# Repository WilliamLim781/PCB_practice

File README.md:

# PCB_practice
just a bunch of PCB practice. That's it

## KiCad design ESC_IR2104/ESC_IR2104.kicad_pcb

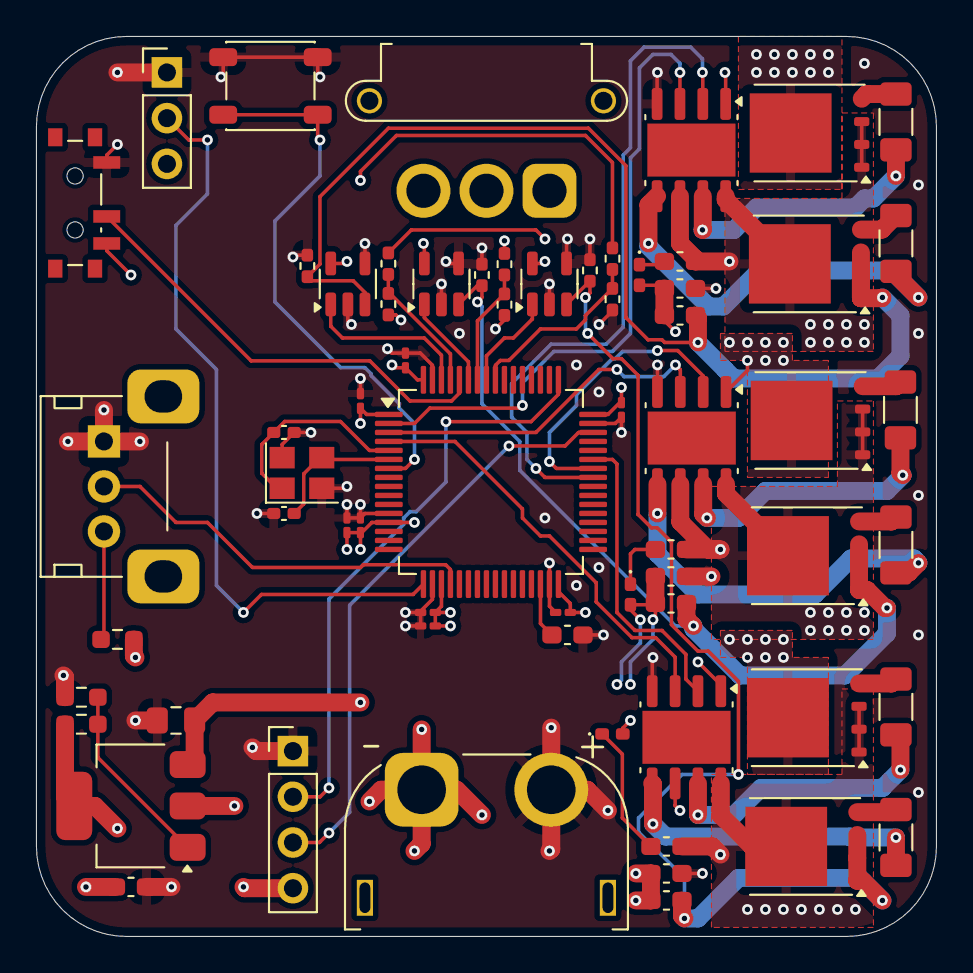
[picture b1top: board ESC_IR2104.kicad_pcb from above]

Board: 6 copper layers, 50.0 x 50.0 mm, 65 parts (0 on the bottom side), 47 nets.

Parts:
C1: 4.7u; C_0201_0603Metric_Pad0.64x0.40mm_HandSolder
C2, C3, C4, C5, C6, C7: 100n; C_0201_0603Metric_Pad0.64x0.40mm_HandSolder
C8: 1u; C_0201_0603Metric_Pad0.64x0.40mm_HandSolder
C9, C10: 8p; C_0402_1005Metric_Pad0.74x0.62mm_HandSolder
C11, C16, C19, C22: 4u7; C_0603_1608Metric_Pad1.08x0.95mm_HandSolder
C12: 10u; C_0805_2012Metric_Pad1.18x1.45mm_HandSolder
C13: 22u; C_0603_1608Metric_Pad1.08x0.95mm_HandSolder
C14, C17, C20: 100n 50V; C_0603_1608Metric_Pad1.08x0.95mm_HandSolder
C15: .27u 50v; C_0603_1608Metric_Pad1.08x0.95mm_HandSolder
C18, C21: .027u 50v; C_0603_1608Metric_Pad1.08x0.95mm_HandSolder
D1, D2, D3: D; D_0402_1005Metric_Pad0.77x0.64mm_HandSolder
J1: swd; PinHeader_1x04_P2.54mm_Vertical
J2: input; PinHeader_1x03_P2.54mm_Vertical
J3: Conn_01x03; AMASS_MR30PW-FB_1x03_P3.50mm_Horizontal
J4: Conn_01x02_Socket; AMASS_XT60PW-F_1x02_P7.20mm_Horizontal
Q1, Q2, Q3, Q4, Q5, Q6: BSC028N06LS3; TDSON-8-1
R1: Current limiter; R_0603_1608Metric_Pad0.98x0.95mm_HandSolder
R2: 10k; R_0603_1608Metric_Pad0.98x0.95mm_HandSolder
R3: 11k; R_0603_1608Metric_Pad0.98x0.95mm_HandSolder
R4, R5, R9, R10, R14, R15: 100; R_1206_3216Metric_Pad1.30x1.75mm_HandSolder
R6, R11, R16: 100k; R_0402_1005Metric_Pad0.72x0.64mm_HandSolder
R7, R12, R17: 2m; R_0402_1005Metric_Pad0.72x0.64mm_HandSolder
R8, R13, R18: 22K; R_0402_1005Metric_Pad0.72x0.64mm_HandSolder
RV1: pot; Potentiometer_Alps_RK09K_Single_Horizontal
SW1: NRST; SW_SPST_PTS647_Sx38
SW2: Boot0; SW_SPDT_PCM12
U1: STM32F411RETx; LQFP-64_10x10mm_P0.5mm
U2: AMS1117; SOT-223-3_TabPin2
U3, U5, U7: IR2104; SOIC-8-1EP_3.9x4.9mm_P1.27mm_EP2.95x4.9mm_Mask2.71x3.4mm
U4, U6, U8: INA180A1; SOT-23-5
Y1: 16Mhz?; Crystal_SMD_3225-4Pin_3.2x2.5mm

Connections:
+3.3V: C1.1, C2.1, C3.1, C4.1, C5.1, C6.1, C7.1, C8.1, C13.1, J1.4, J2.3, R1.1, R2.1, SW2.3 (C), U1.1 (VBAT), U1.13 (VDDA), U1.19 (VDD), U1.32 (VDD), U1.48 (VDD), U1.64 (VDD), U2.2 (VO), U4.5 (V+), U6.5 (V+), U8.5 (V+)
/ADC1_IN4: RV1.2, U1.20 (PA4)
/MosFet TIM_1_PhaseA/LowsideA: C16.2, Q2.1 (S), Q2.2 (S), Q2.3 (S), R7.1, U4.3 (+)
/MosFet TIM_1_PhaseB/LowsideA: C19.2, Q4.1 (S), Q4.2 (S), Q4.3 (S), R12.1, U6.3 (+)
/MosFet TIM_1_PhaseC/LowsideA: C22.2, Q6.1 (S), Q6.2 (S), Q6.3 (S), R17.1, U8.3 (+)
GND: C1.2, C2.2, C3.2, C4.2, C5.2, C6.2, C7.2, C8.2, C9.2, C10.2, C11.2, C12.2, C13.2, C14.1, C17.1, C20.1, J1.1, J2.1, J4.2, R3.2, R7.2, R8.2, R12.2, R13.2, R17.2, R18.2, RV1.1, SW1.1 (A), SW2.1 (A), U1.12 (VSSA), U1.18 (VSS), U1.31 (VSS), U1.47 (VSS), U1.63 (VSS), U3.4 (COM), U4.2 (GND), U4.4 (-), U5.4 (COM), U6.2 (GND), U6.4 (-), U7.4 (COM), U8.2 (GND), U8.4 (-), Y1.2, Y1.4
HSE_IN: C9.1, U1.5 (PH0), Y1.1
HSE_OUT: C10.1, U1.6 (PH1), Y1.3
unnamed: C15.2, D1.1 (K)
unnamed: C18.2, D2.1 (K)
unnamed: C21.2, D3.1 (K)
unnamed: Q1.4 (G), R4.1
unnamed: Q2.4 (G), R5.2
unnamed: Q3.4 (G), R9.2
unnamed: Q4.4 (G), R10.2
unnamed: Q5.4 (G), R14.2
unnamed: Q6.4 (G), R15.2
unnamed: R1.2, RV1.3
unnamed: SW1.2 (B), U1.7 (NRST)
unnamed: SW2.2 (B), U1.60 (BOOT0)
unnamed: C11.1, U1.30 (VCAP1)
unnamed: R2.2, R3.1, U2.1 (ADJ)
unnamed: R4.2, U3.7 (HO)
unnamed: R5.1, U3.5 (LO)
unnamed: R9.1, U5.7 (HO)
unnamed: R10.1, U5.5 (LO)
unnamed: R14.1, U7.7 (HO)
unnamed: R15.1, U7.5 (LO)
PhaseA: C15.1, J3.1, Q1.1 (S), Q1.2 (S), Q1.3 (S), Q2.5 (D), R6.1, U3.6 (VS), U3.8 (VB)
PhaseA_Current_sense: U1.62 (PB9), U4.1
PhaseA_SD: U1.2 (PC13), U3.3 (~SD)
PhaseA_Voltage_sense: R6.2, R8.1, U1.61 (PB8)
PhaseB: C18.1, J3.2, Q3.1 (S), Q3.2 (S), Q3.3 (S), Q4.5 (D), R11.1, U5.6 (VS), U5.8 (VB)
PhaseB_Current_sense: U1.59 (PB7), U6.1
PhaseB_SD: U1.3 (PC14), U5.3 (~SD)
PhaseB_Voltage_sense: R11.2, R13.1, U1.58 (PB6)
PhaseC: C21.1, J3.3, Q5.1 (S), Q5.2 (S), Q5.3 (S), Q6.5 (D), R16.1, U7.6 (VS), U7.8 (VB)
PhaseC_Current_sense: U1.57 (PB5), U8.1
PhaseC_SD: U1.4 (PC15), U7.3 (~SD)
PhaseC_Voltage_sense: R16.2, R18.1, U1.56 (PB4)
SWCLK: J1.2, U1.49 (PA14)
SWDIO: J1.3, U1.46 (PA13)
TIM1_CH1: U1.41 (PA8), U3.2 (IN)
TIM1_CH2: U1.42 (PA9), U5.2 (IN)
TIM1_CH3: U1.43 (PA10), U7.2 (IN)
TIM9_CH2_input: J2.2, U1.17 (PA3)
VCC: C12.1, C14.2, C16.1, C17.2, C19.1, C20.2, C22.1, D1.2 (A), D2.2 (A), D3.2 (A), J4.1, Q1.5 (D), Q3.5 (D), Q5.5 (D), U2.3 (VI), U3.1 (VCC), U5.1 (VCC), U7.1 (VCC)

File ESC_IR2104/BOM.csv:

Designator,Comment,Footprint,JLCPCB Part #
C1,4.7u,Capacitor_SMD:C_0201_0603Metric_Pad0.64x0.40mm_HandSolder,C335103
"C2,C3,C4,C5,C6,C7",100n,Capacitor_SMD:C_0201_0603Metric_Pad0.64x0.40mm_HandSolder,C49062
C8,1u,Capacitor_SMD:C_0201_0603Metric_Pad0.64x0.40mm_HandSolder,C53067
"C9,C10",C,Capacitor_SMD:C_0402_1005Metric_Pad0.74x0.62mm_HandSolder,C1578
"C11,C16,C19,C22",4u7,Capacitor_SMD:C_0603_1608Metric_Pad1.08x0.95mm_HandSolder,C19666
C12,10u,Capacitor_SMD:C_0805_2012Metric_Pad1.18x1.45mm_HandSolder,C15850
C13,22u,Capacitor_SMD:C_0603_1608Metric_Pad1.08x0.95mm_HandSolder,C59461
"C14,C17,C20",100n 50V,Capacitor_SMD:C_0603_1608Metric_Pad1.08x0.95mm_HandSolder,C14663
"C15,C18,C21",.027u 50v,Capacitor_SMD:C_0603_1608Metric_Pad1.08x0.95mm_HandSolder,C15849
"D1,D2,D3",D,Diode_SMD:D_0402_1005Metric_Pad0.77x0.64mm_HandSolder,
J1,swd,Connector_PinHeader_2.54mm:PinHeader_1x04_P2.54mm_Vertical,
J2,input,Connector_PinHeader_2.54mm:PinHeader_1x03_P2.54mm_Vertical,
J3,Conn_01x03,Connector_AMASS:AMASS_MR30PW-FB_1x03_P3.50mm_Horizontal,
J4,Conn_01x02_Socket,Connector_AMASS:AMASS_XT60PW-F_1x02_P7.20mm_Horizontal,
"Q1,Q2,Q3,Q4,Q5,Q6",BSC028N06LS3,Package_TO_SOT_SMD:TDSON-8-1,C5804631
R1,Current limiter,Resistor_SMD:R_0603_1608Metric_Pad0.98x0.95mm_HandSolder,C21190
R2,10k,Resistor_SMD:R_0603_1608Metric_Pad0.98x0.95mm_HandSolder,C25804
R3,11k,Resistor_SMD:R_0603_1608Metric_Pad0.98x0.95mm_HandSolder,C25950
"R4,R5,R9,R10,R14,R15",100,Resistor_SMD:R_0805_2012Metric_Pad1.20x1.40mm_HandSolder,C17901
"R6,R11,R16",100k,Resistor_SMD:R_0402_1005Metric_Pad0.72x0.64mm_HandSolder,C25741
"R7,R12,R17",2m,Resistor_SMD:R_0402_1005Metric_Pad0.72x0.64mm_HandSolder,
"R8,R13,R18",22K,Resistor_SMD:R_0402_1005Metric_Pad0.72x0.64mm_HandSolder,C25768
RV1,pot,Potentiometer_THT:Potentiometer_Alps_RK09K_Single_Horizontal,
SW1,NRST,Button_Switch_SMD:SW_SPST_PTS647_Sx38,
SW2,Boot0,Button_Switch_SMD:SW_SPDT_PCM12,
U1,STM32F411RETx,Package_QFP:LQFP-64_10x10mm_P0.5mm,C94355
U2,AMS1117,Package_TO_SOT_SMD:SOT-223-3_TabPin2,
"U3,U5,U7",IR2104,Package_SO:SOIC-8-1EP_3.9x4.9mm_P1.27mm_EP2.95x4.9mm_Mask2.71x3.4mm,
"U4,U6,U8",INA180A1,Package_TO_SOT_SMD:SOT-23-5,
Y1,16Mhz?,Crystal:Crystal_SMD_3225-4Pin_3.2x2.5mm,C13738

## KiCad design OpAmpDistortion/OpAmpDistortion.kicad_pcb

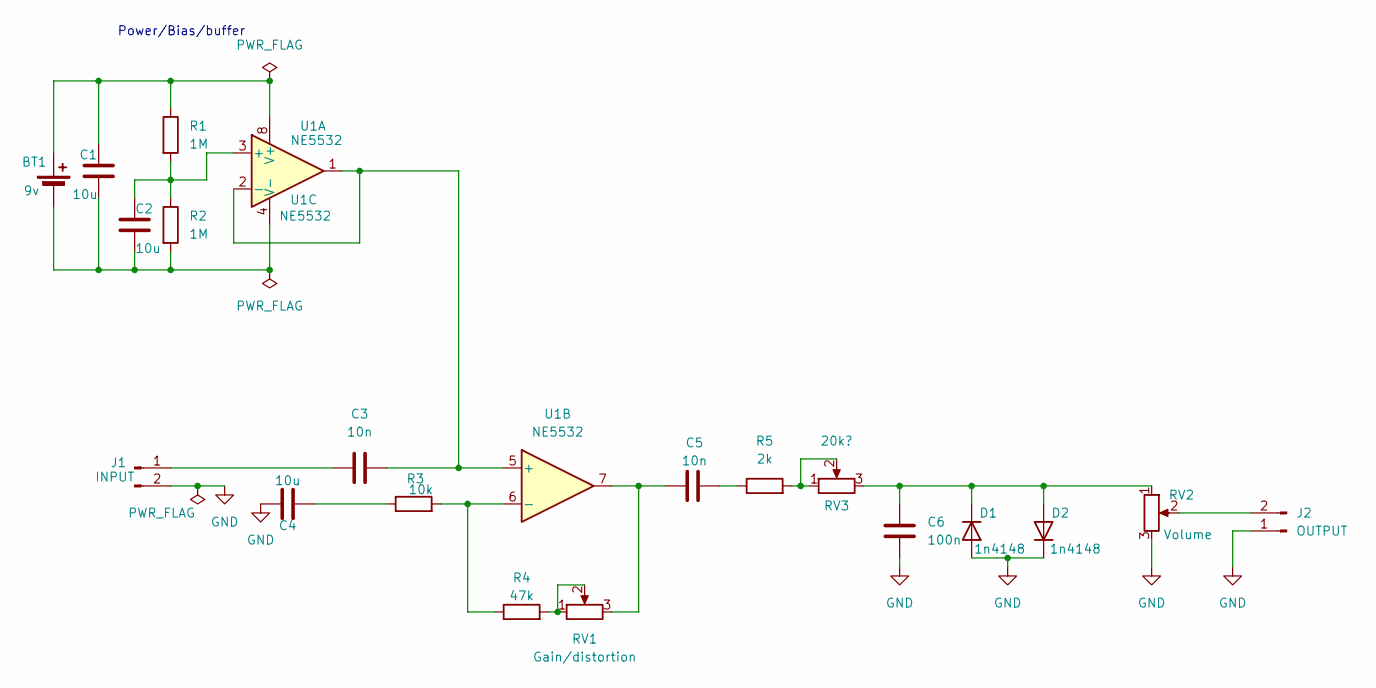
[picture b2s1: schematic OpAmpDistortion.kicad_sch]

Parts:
BT1: 9v; PinHeader_1x02_P2.54mm_Vertical
C1, C2, C4: 10u; C_0603_1608Metric_Pad1.08x0.95mm_HandSolder
C3, C5: 10n; C_0603_1608Metric_Pad1.08x0.95mm_HandSolder
C6: 100n; C_0603_1608Metric_Pad1.08x0.95mm_HandSolder
D1, D2: 1n4148; D_0603_1608Metric_Pad1.05x0.95mm_HandSolder
J1: INPUT; PinHeader_1x02_P2.54mm_Vertical
J2: OUTPUT; PinHeader_1x02_P2.54mm_Vertical
R1, R2: 1M; R_0603_1608Metric_Pad0.98x0.95mm_HandSolder
R3: 10k; R_0603_1608Metric_Pad0.98x0.95mm_HandSolder
R4: 47k; R_0603_1608Metric_Pad0.98x0.95mm_HandSolder
R5: 2k; R_0603_1608Metric_Pad0.98x0.95mm_HandSolder
RV1: Gain/distortion; PinHeader_1x03_P2.54mm_Vertical
RV2: Volume; PinHeader_1x03_P2.54mm_Vertical
RV3: 20k?; PinHeader_1x03_P2.54mm_Vertical
U1: NE5532; DIP-8_W7.62mm_LongPads

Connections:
GND: C4.1, C6.2, D1.2 (A), D2.1 (K), J1.2, J2.1, RV2.3
unnamed: BT1.1 (+), C1.1, R1.1, U1.8 (V+)
unnamed: BT1.2 (-), C1.2, C2.2, R2.2, U1.4 (V-)
unnamed: C4.2, R3.1
unnamed: C5.1, RV1.3, U1.7
unnamed: C5.2, R5.1
unnamed: C6.1, D1.1 (K), D2.2 (A), RV2.1, RV3.3
unnamed: C3.1, J1.1
unnamed: J2.2, RV2.2
unnamed: R4.2, RV1.1, RV1.2
unnamed: R5.2, RV3.1, RV3.2
unnamed: C2.1, R1.2, R2.1, U1.3 (+)
unnamed: C3.2, U1.1, U1.2 (-), U1.5 (+)
unnamed: R3.2, R4.1, U1.6 (-)

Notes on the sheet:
Power/Bias/buffer

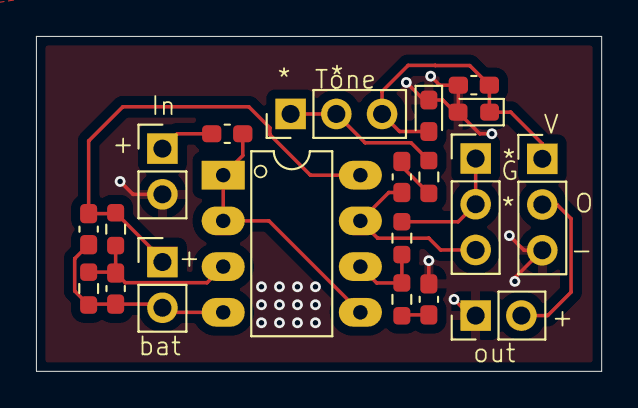
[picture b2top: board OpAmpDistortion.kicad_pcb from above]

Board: 2 copper layers, 31.4 x 18.6 mm, 20 parts (0 on the bottom side), 14 nets.

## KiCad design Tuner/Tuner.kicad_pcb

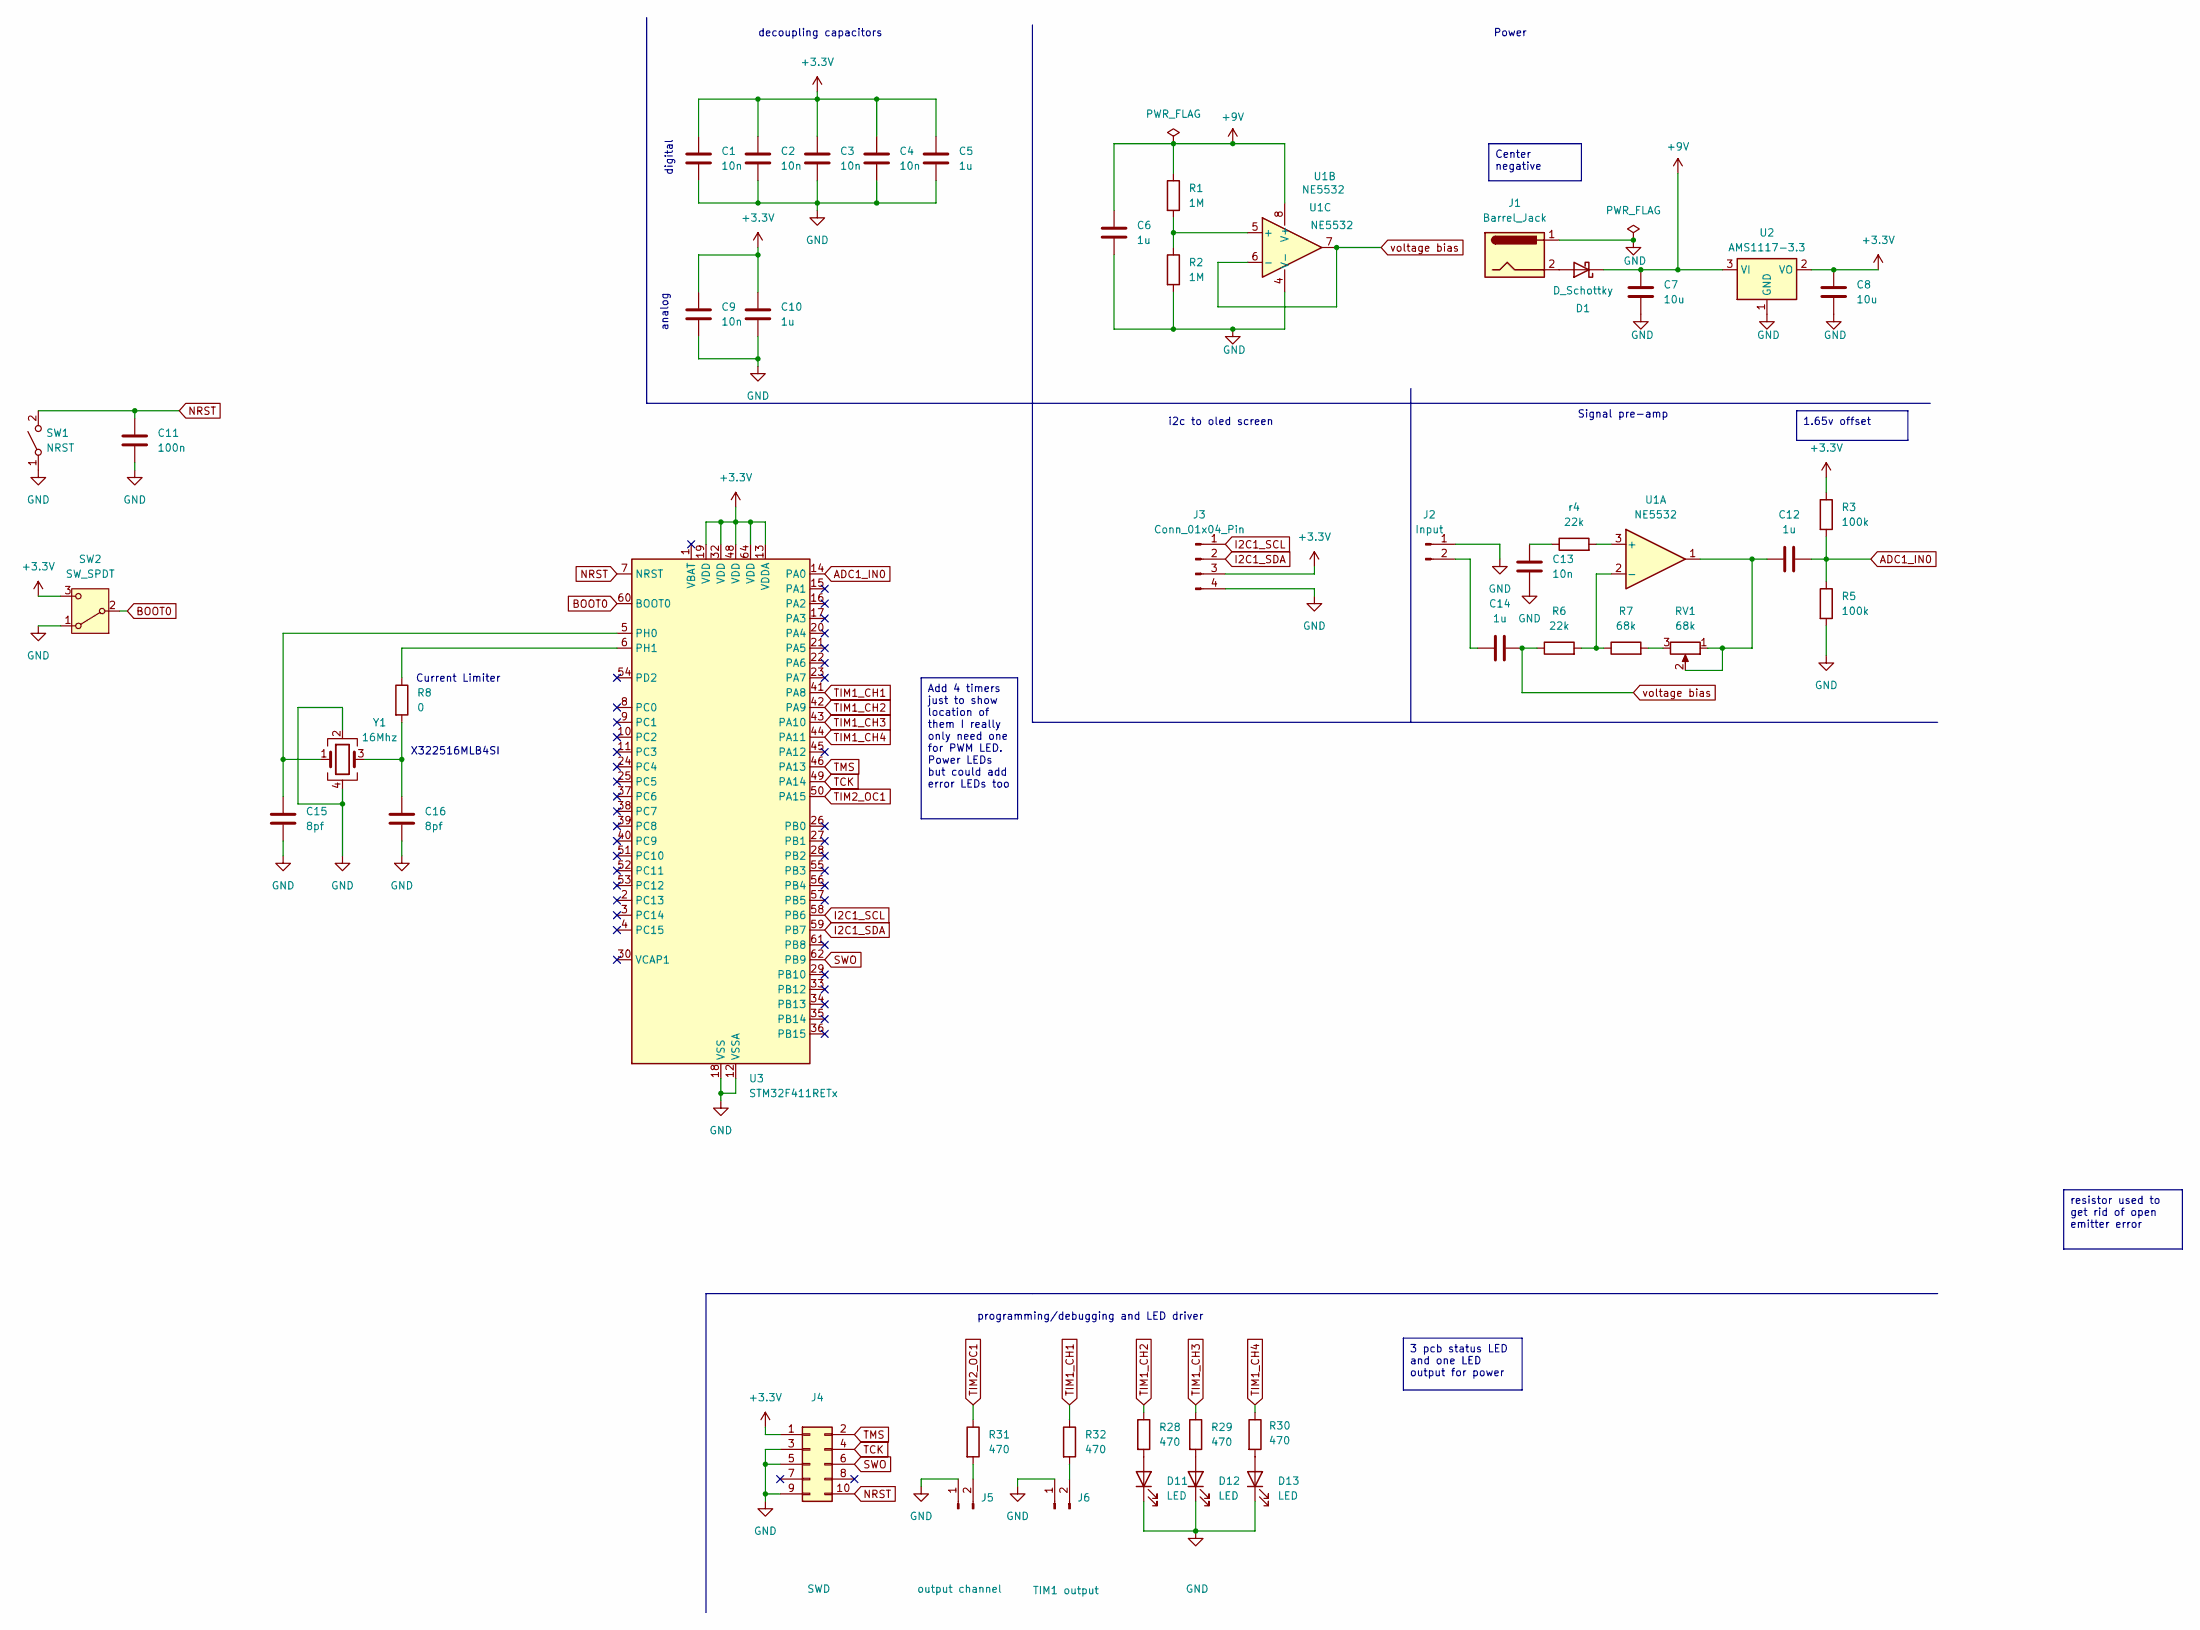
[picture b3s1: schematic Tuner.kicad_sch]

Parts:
C1, C2, C3, C4, C9, C13: 10n; C_0603_1608Metric_Pad1.08x0.95mm_HandSolder
C5, C6, C10, C12, C14: 1u; C_0603_1608Metric_Pad1.08x0.95mm_HandSolder
C7, C8: 10u; C_0603_1608Metric_Pad1.08x0.95mm_HandSolder
C11: 100n; C_0603_1608Metric_Pad1.08x0.95mm_HandSolder
C15, C16: 8pf; C_0603_1608Metric_Pad1.08x0.95mm_HandSolder
D1: D_Schottky; D_0603_1608Metric_Pad1.05x0.95mm_HandSolder
D11, D12, D13: LED; LED_1206_3216Metric_Pad1.42x1.75mm_HandSolder
J1: Barrel_Jack; PinHeader_1x02_P2.54mm_Vertical
J2: Input; PinHeader_1x02_P2.54mm_Vertical
J3: Conn_01x04_Pin; PinHeader_1x04_P2.54mm_Vertical
J4: SWD; PinHeader_2x05_P2.54mm_Vertical
J5: output channel; PinHeader_1x02_P2.54mm_Vertical
J6: TIM1 output; PinHeader_1x02_P2.54mm_Vertical
R1, R2: 1M; R_0603_1608Metric_Pad0.98x0.95mm_HandSolder
R3, R5: 100k; R_0603_1608Metric_Pad0.98x0.95mm_HandSolder
R6: 22k; R_0603_1608Metric_Pad0.98x0.95mm_HandSolder
R7: 68k; R_0603_1608Metric_Pad0.98x0.95mm_HandSolder
R8: 0; R_0603_1608Metric_Pad0.98x0.95mm_HandSolder
R28, R29, R30, R31, R32: 470; R_0603_1608Metric_Pad0.98x0.95mm_HandSolder
RV1: 68k; PinHeader_1x03_P2.54mm_Vertical
SW1: NRST; SW_PUSH_6mm
SW2: SW_SPDT; SW_SPDT_PCM12
U1: NE5532; DIP-8_W7.62mm
U2: AMS1117-3.3; SOT-223-3_TabPin2
U3: STM32F411RETx; LQFP-64_10x10mm_P0.5mm
Y1: 16Mhz; Crystal_SMD_3225-4Pin_3.2x2.5mm_HandSoldering
r4: 22k; R_0603_1608Metric_Pad0.98x0.95mm_HandSolder

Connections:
+3.3V: C1.1, C2.1, C3.1, C4.1, C5.1, C8.1, C9.1, C10.1, J3.3, J4.1, R3.1, SW2.3 (C), U2.2 (VO), U3.13 (VDDA), U3.19 (VDD), U3.32 (VDD), U3.48 (VDD), U3.64 (VDD)
+9V: C6.1, C7.1, D1.1 (K), R1.1, U1.8 (V+), U2.3 (VI)
ADC1_IN0: C12.2, R3.2, R5.1, U3.14 (PA0)
BOOT0: SW2.2 (B), U3.60 (BOOT0)
GND: C1.2, C2.2, C3.2, C4.2, C5.2, C6.2, C7.2, C8.2, C9.2, C10.2, C11.2, C13.2, C15.2, C16.2, D11.1 (K), D12.1 (K), D13.1 (K), J1.1, J2.1, J3.4, J4.3, J4.5, J4.9, J5.1, J6.1, R2.2, R5.2, SW1.1 (A), SW2.1 (A), U1.4 (V-), U2.1 (GND), U3.12 (VSSA), U3.18 (VSS), U3.31 (VSS), U3.47 (VSS), U3.63 (VSS), Y1.2, Y1.4
I2C1_SCL: J3.1, U3.58 (PB6)
I2C1_SDA: J3.2, U3.59 (PB7)
NRST: C11.1, J4.10, SW1.2 (B), U3.7 (NRST)
unnamed: C12.1, RV1.1, RV1.2, U1.1
unnamed: C13.1, r4.1
unnamed: C16.1, R8.2, Y1.3
unnamed: D1.2 (A), J1.2
unnamed: D11.2 (A), R28.2
unnamed: D12.2 (A), R29.2
unnamed: D13.2 (A), R30.2
unnamed: C14.1, J2.2
unnamed: J5.2, R31.2
unnamed: J6.2, R32.2
unnamed: R7.2, RV1.3
unnamed: U1.3 (+), r4.2
unnamed: R6.2, R7.1, U1.2 (-)
unnamed: R1.2, R2.1, U1.5 (+)
unnamed: C15.1, U3.5 (PH0), Y1.1
unnamed: R8.1, U3.6 (PH1)
SWO: J4.6, U3.62 (PB9)
TCK: J4.4, U3.49 (PA14)
TIM1_CH1: R32.1, U3.41 (PA8)
TIM1_CH2: R28.1, U3.42 (PA9)
TIM1_CH3: R29.1, U3.43 (PA10)
TIM1_CH4: R30.1, U3.44 (PA11)
TIM2_OC1: R31.1, U3.50 (PA15)
TMS: J4.2, U3.46 (PA13)
voltage bias: C14.2, R6.1, U1.6 (-), U1.7

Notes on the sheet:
Center negative
3 pcb status LED and one LED output for power
resistor used to get rid of open emitter error
Add 4 timers just to show location of them I really only need one for PWM LED. Power LEDs but could add error LEDs too
1.65v offset
Current Limiter
Signal pre-amp
decoupling capacitors
Power
programming/debugging and LED driver
analog
X322516MLB4SI
i2c to oled screen
digital

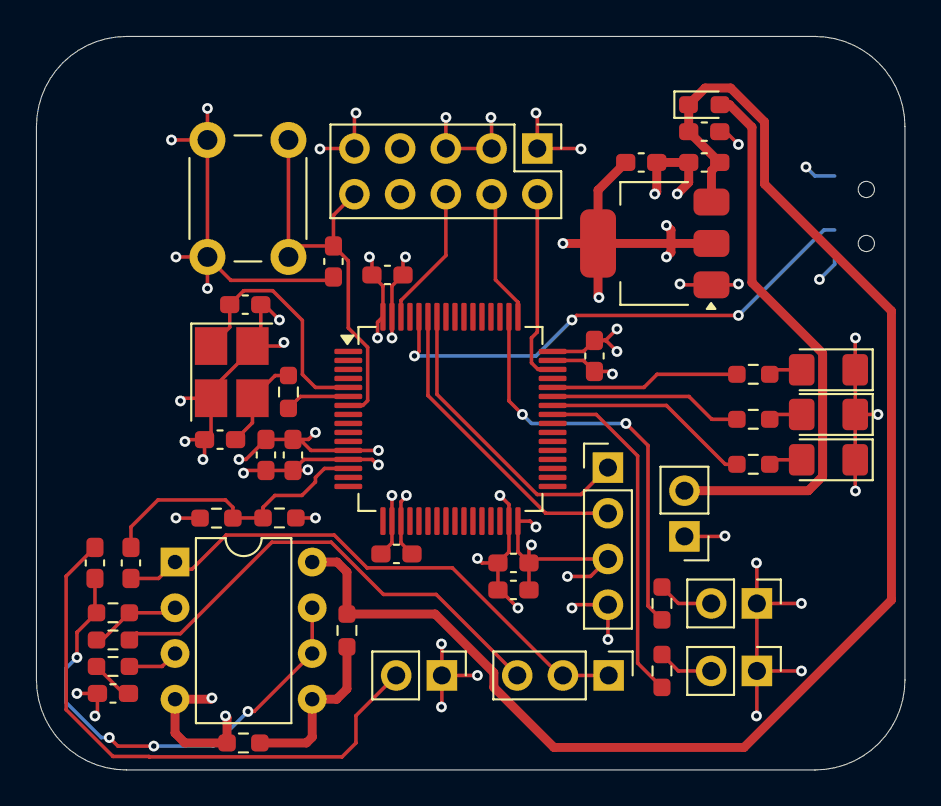
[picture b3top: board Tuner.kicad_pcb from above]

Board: 4 copper layers, 48.2 x 40.8 mm, 46 parts (1 on the bottom side), 33 nets.

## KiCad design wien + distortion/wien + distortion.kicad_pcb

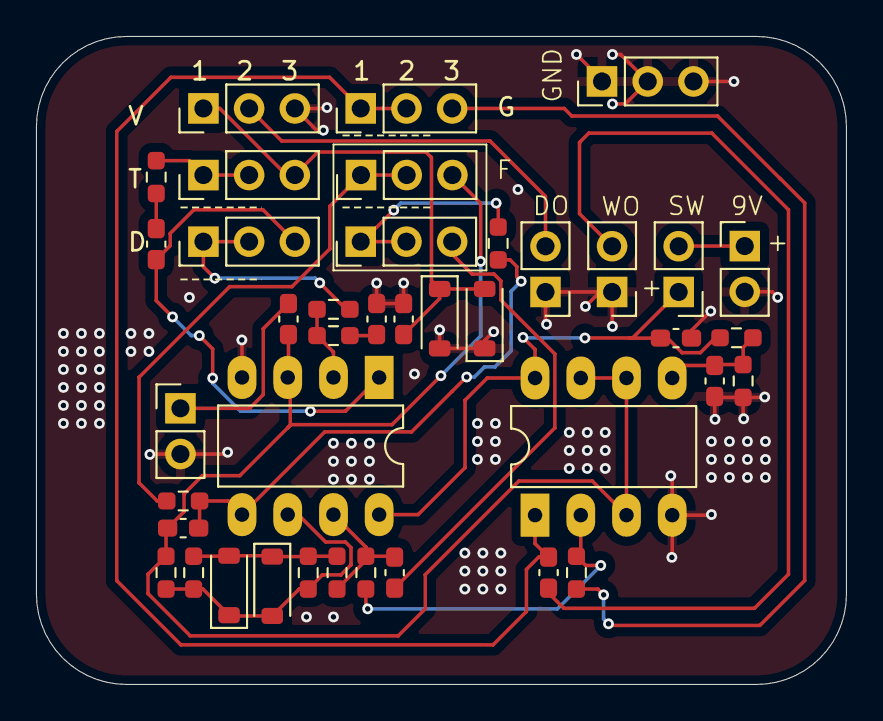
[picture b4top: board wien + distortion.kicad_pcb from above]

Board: 2 copper layers, 45.0 x 36.0 mm, 40 parts (0 on the bottom side), 25 nets.

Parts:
BT1: 9V; PinHeader_1x02_P2.54mm_Vertical
C1, C2: 10n; C_0603_1608Metric_Pad1.08x0.95mm_HandSolder
C3: 10u; C_0603_1608Metric_Pad1.08x0.95mm_HandSolder
C4, C5, C7, C8: 100n; C_0603_1608Metric_Pad1.08x0.95mm_HandSolder
C6, C9: 1u?; C_0603_1608Metric_Pad1.08x0.95mm_HandSolder
D1, D2, D3, D4: 1n4148; D_SOD-123
DualPot1: 100k; PinHeader_1x03_P2.54mm_Vertical
J1: INPUT; PinHeader_1x02_P2.54mm_Vertical
J2, J5: OUTPUT; PinHeader_1x02_P2.54mm_Vertical
J4: PWR switch; PinHeader_1x02_P2.54mm_Vertical
J6: GND connections; PinHeader_1x03_P2.54mm_Vertical
R1: 2k; R_0603_1608Metric_Pad0.98x0.95mm_HandSolder
R2, R12: 10k; R_0603_1608Metric_Pad0.98x0.95mm_HandSolder
R3: 47k; R_0603_1608Metric_Pad0.98x0.95mm_HandSolder
R4, R5: 4k7; R_0603_1608Metric_Pad0.98x0.95mm_HandSolder
R6, R7: 2k2; R_0603_1608Metric_Pad0.98x0.95mm_HandSolder
R8, R10: 100; R_0603_1608Metric_Pad0.98x0.95mm_HandSolder
R9, R11: 1M; R_0603_1608Metric_Pad0.98x0.95mm_HandSolder
R13: 100?; R_0603_1608Metric_Pad0.98x0.95mm_HandSolder
RV1: 20k? tone; PinHeader_1x03_P2.54mm_Vertical
RV2: Volume; PinHeader_1x03_P2.54mm_Vertical
RV3: Gain/distortion; PinHeader_1x03_P2.54mm_Vertical
RV4: DualPot2; PinHeader_1x03_P2.54mm_Vertical
RV5: Gain10k?; PinHeader_1x03_P2.54mm_Vertical
U1, U2: NE5532; DIP-8_W7.62mm_LongPads

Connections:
+9V: C6.1, J4.1, R9.1, U1.8 (V+), U2.8 (V+)
BiasVoltage: C1.2, C7.2, DualPot1.3, R6.1, U1.3 (+), U2.3 (+), U2.6 (-), U2.7
GND: BT1.2 (-), C3.1, C4.2, C6.2, C9.2, D1.2 (A), D2.1 (K), J1.2, J2.1, J5.1, J6.1, J6.2, J6.3, R11.2, RV2.3, U1.4 (V-), U2.4 (V-)
unnamed: BT1.1 (+), J4.2
unnamed: C2.1, RV3.3, U1.1
unnamed: C2.2, R1.1
unnamed: C3.2, R2.1
unnamed: C5.1, R7.2, R12.1, U1.7
unnamed: C5.2, RV4.3
unnamed: C8.1, RV5.1, RV5.2, U2.1
unnamed: C4.1, D1.1 (K), D2.2 (A), RV1.3, RV2.1
unnamed: D3.2 (A), D4.1 (K), R4.2, R5.2, R7.1
unnamed: D3.1 (K), D4.2 (A), R4.1, R5.1, R6.2, U1.6 (-)
unnamed: DualPot1.1, DualPot1.2, R10.1
unnamed: C1.1, J1.1
unnamed: J2.2, RV2.2
unnamed: C8.2, J5.2
unnamed: R1.2, RV1.1, RV1.2
unnamed: R3.2, RV3.1, RV3.2
unnamed: R8.2, RV4.1, RV4.2
unnamed: R13.2, RV5.3
unnamed: R2.2, R3.1, U1.2 (-)
unnamed: C7.1, R8.1, R10.2, U1.5 (+)
unnamed: R12.2, R13.1, U2.2 (-)
unnamed: C9.1, R9.2, R11.1, U2.5 (+)

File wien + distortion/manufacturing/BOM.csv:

Comment,Designator,Footprint,JLCPCB Part#
9V,BT1,Connector_PinHeader_2.54mm:PinHeader_1x02_P2.54mm_Vertical,
10n,"C1,C2",Capacitor_SMD:C_0603_1608Metric_Pad1.08x0.95mm_HandSolder,C57112
10u,C3,Capacitor_SMD:C_0603_1608Metric_Pad1.08x0.95mm_HandSolder,C96446
100n,"C4,C5,C7,C8",Capacitor_SMD:C_0603_1608Metric_Pad1.08x0.95mm_HandSolder,C14663
1u?,"C6,C9",Capacitor_SMD:C_0603_1608Metric_Pad1.08x0.95mm_HandSolder,C15849
1n4148,"D1,D2,D3,D4",Diode_SMD:D_SOD-123,C81598
100k,DualPot1,Connector_PinHeader_2.54mm:PinHeader_1x03_P2.54mm_Vertical,
INPUT,J1,Connector_PinHeader_2.54mm:PinHeader_1x02_P2.54mm_Vertical,
OUTPUT,"J2,J5",Connector_PinHeader_2.54mm:PinHeader_1x02_P2.54mm_Vertical,
PWR switch,J4,Connector_PinHeader_2.54mm:PinHeader_1x02_P2.54mm_Vertical,
GND connections,J6,Connector_PinHeader_2.54mm:PinHeader_1x03_P2.54mm_Vertical,
2k,R1,Resistor_SMD:R_0603_1608Metric_Pad0.98x0.95mm_HandSolder,C4190
10k,"R2,R12",Resistor_SMD:R_0603_1608Metric_Pad0.98x0.95mm_HandSolder,C25804
47k,R3,Resistor_SMD:R_0603_1608Metric_Pad0.98x0.95mm_HandSolder,C25819
4k7,"R4,R5",Resistor_SMD:R_0603_1608Metric_Pad0.98x0.95mm_HandSolder,C23162
2k2,"R6,R7",Resistor_SMD:R_0603_1608Metric_Pad0.98x0.95mm_HandSolder,C4190
100,"R8,R10",Resistor_SMD:R_0603_1608Metric_Pad0.98x0.95mm_HandSolder,C22775
1M,"R9,R11",Resistor_SMD:R_0603_1608Metric_Pad0.98x0.95mm_HandSolder,C22935
100?,R13,Resistor_SMD:R_0603_1608Metric_Pad0.98x0.95mm_HandSolder,C22775
20k? tone,RV1,Connector_PinHeader_2.54mm:PinHeader_1x03_P2.54mm_Vertical,
Volume,RV2,Connector_PinHeader_2.54mm:PinHeader_1x03_P2.54mm_Vertical,
Gain/distortion,RV3,Connector_PinHeader_2.54mm:PinHeader_1x03_P2.54mm_Vertical,
DualPot2,RV4,Connector_PinHeader_2.54mm:PinHeader_1x03_P2.54mm_Vertical,
Gain10k?,RV5,Connector_PinHeader_2.54mm:PinHeader_1x03_P2.54mm_Vertical,
NE5532,"U1,U2",Package_DIP:DIP-8_W7.62mm_LongPads,

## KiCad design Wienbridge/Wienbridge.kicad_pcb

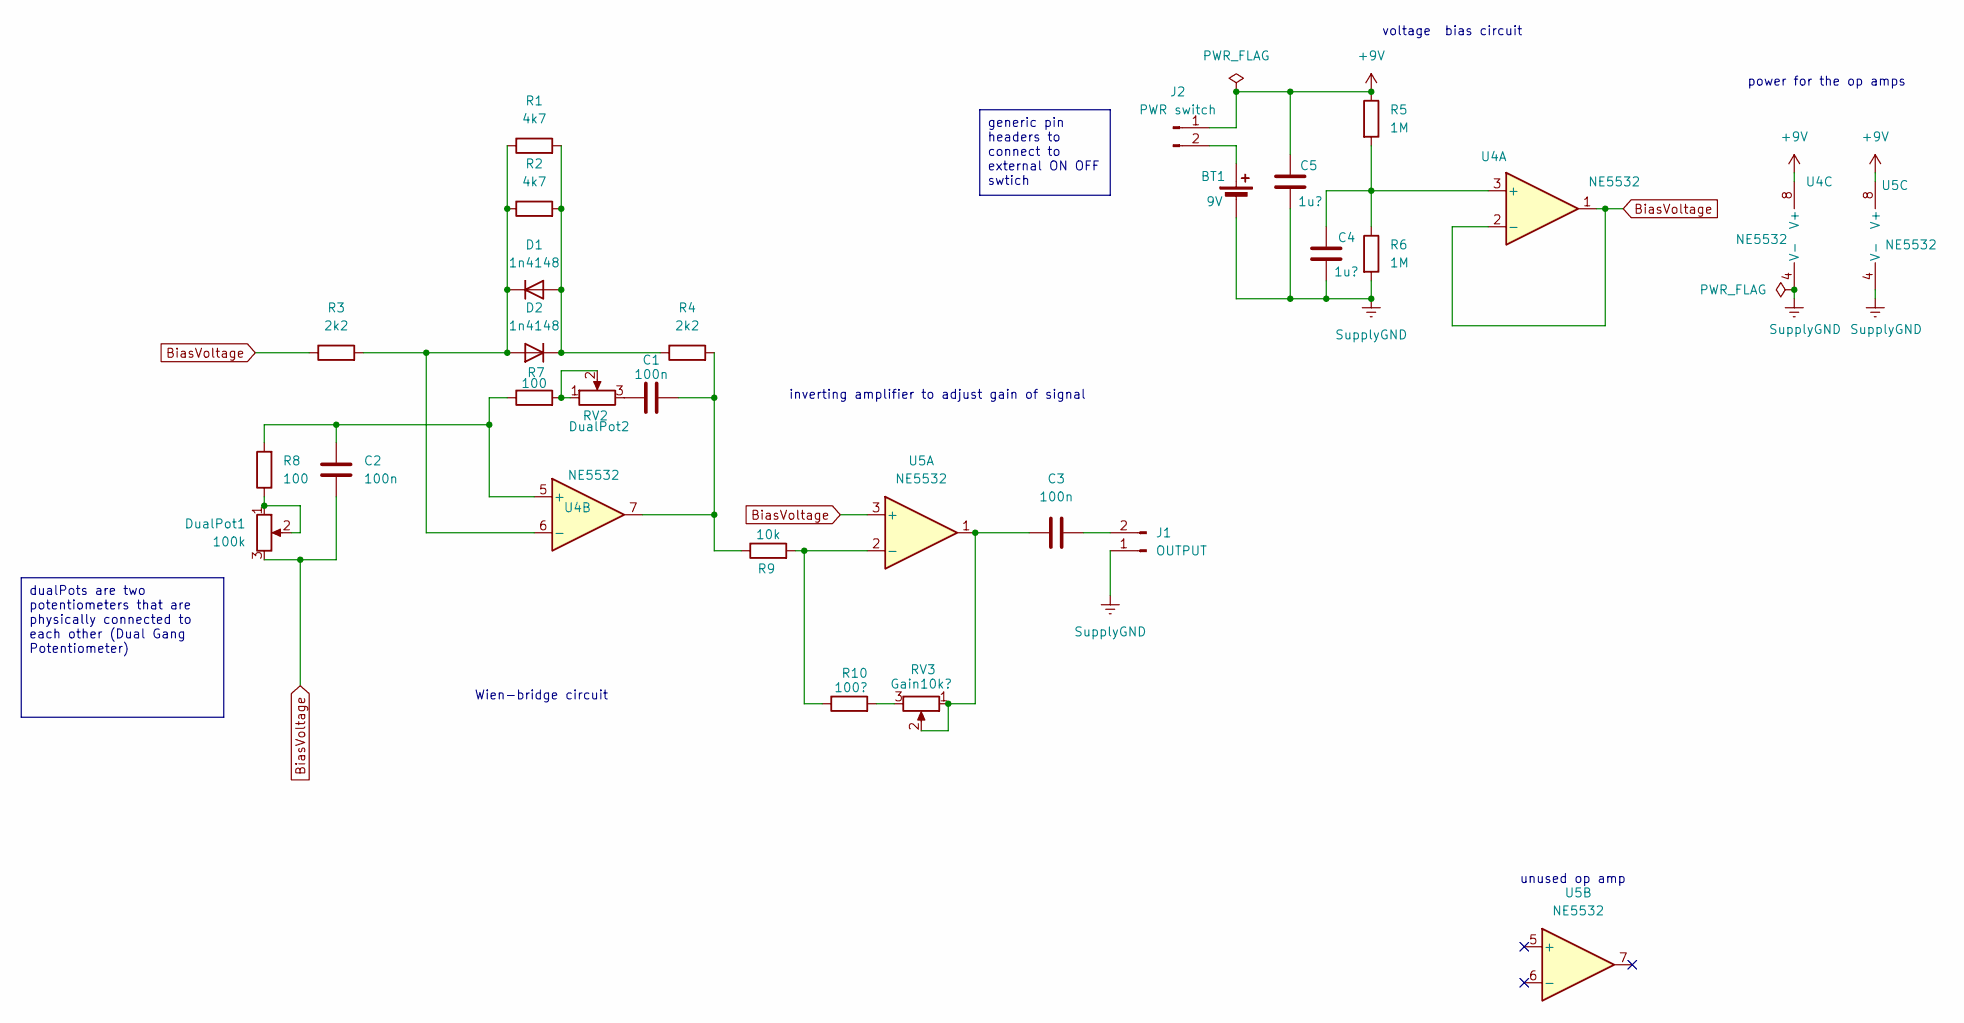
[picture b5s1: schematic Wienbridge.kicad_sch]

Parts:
BT1: 9V; PinHeader_1x02_P2.54mm_Vertical
C1, C2, C3: 100n; C_0603_1608Metric_Pad1.08x0.95mm_HandSolder
C4, C5: 1u?; C_0603_1608Metric_Pad1.08x0.95mm_HandSolder
D1, D2: 1n4148; D_0603_1608Metric_Pad1.05x0.95mm_HandSolder
DualPot1: 100k; PinHeader_1x03_P2.54mm_Vertical
J1: OUTPUT; PinHeader_1x02_P2.54mm_Vertical
J2: PWR switch; PinHeader_1x02_P2.54mm_Vertical
R1, R2: 4k7; R_0603_1608Metric_Pad0.98x0.95mm_HandSolder
R3, R4: 2k2; R_0603_1608Metric_Pad0.98x0.95mm_HandSolder
R5, R6: 1M; R_0603_1608Metric_Pad0.98x0.95mm_HandSolder
R7, R8: 100; R_0603_1608Metric_Pad0.98x0.95mm_HandSolder
R9: 10k; R_0603_1608Metric_Pad0.98x0.95mm_HandSolder
R10: 100?; R_0603_1608Metric_Pad0.98x0.95mm_HandSolder
RV2: DualPot2; PinHeader_1x03_P2.54mm_Vertical
RV3: Gain10k?; PinHeader_1x03_P2.54mm_Vertical
U4, U5: NE5532; DIP-8_W7.62mm

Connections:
+9V: C5.1, J2.1, R5.1, U4.8 (V+), U5.8 (V+)
BiasVoltage: C2.2, DualPot1.3, R3.1, U4.1, U4.2 (-), U5.3 (+)
unnamed: BT1.1 (+), J2.2
unnamed: C1.1, RV2.3
unnamed: C1.2, R4.2, R9.1, U4.7
unnamed: C3.1, RV3.1, RV3.2, U5.1
unnamed: D1.2 (A), D2.1 (K), R1.2, R2.2, R4.1
unnamed: D1.1 (K), D2.2 (A), R1.1, R2.1, R3.2, U4.6 (-)
unnamed: DualPot1.1, DualPot1.2, R8.1
unnamed: C3.2, J1.2
unnamed: R7.2, RV2.1, RV2.2
unnamed: R10.2, RV3.3
unnamed: C4.1, R5.2, R6.1, U4.3 (+)
unnamed: C2.1, R7.1, R8.2, U4.5 (+)
unnamed: R9.2, R10.1, U5.2 (-)
SupplyGND: BT1.2 (-), C4.2, C5.2, J1.1, R6.2, U4.4 (V-), U5.4 (V-)

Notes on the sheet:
dualPots are two potentiometers that are physically connected to each other (Dual Gang Potentiometer)
generic pin headers to connect to external ON OFF swtich
unused op amp
power for the op amps
Wien-bridge circuit
voltage bias circuit
inverting amplifier to adjust gain of signal

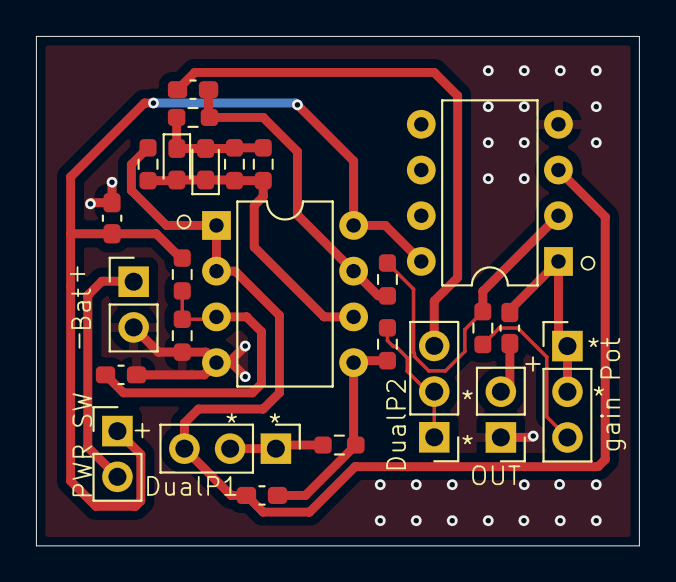
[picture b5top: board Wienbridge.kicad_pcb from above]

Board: 2 copper layers, 33.5 x 28.3 mm, 25 parts (0 on the bottom side), 16 nets.

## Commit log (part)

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2023-09-18 added the basic stm32 F411RE schematics
2023-09-19 changed some footprints in the schemaitcs and also done some PCB layout for the board
2023-09-19 removed the GPIO input and outpins (want to redo them) and mostly finished the first pcb layout
2023-09-26 PCB changes
    changed form factor, finished PCB, and ran DRC
    :wq
2023-09-30 reorganize and add new pcb
2023-10-02 made changes to the HX711 footprints and finihsed the pcb
2023-10-06 added a new pcb practice (F446re)
2023-10-06 idk what this is
2023-10-06 Added connectors for the left half of the f446re need to do the right half
2023-10-08 finished the schematic for the f446re. However, I forgot to add the name for the serial wire debug on the schematic
2023-10-08 tweaked oscillator, fixed serial debug names, added i2c connectors. Also don't forget to add a voltage regulator
2023-10-08 adding some mounting holes
2023-10-08 added a simpler f446re that suppose to be a prototype DAQ
2023-10-12 finished the schematics, added footprints, and started with the pcb
2023-10-13 PCB routing. Need to do USB differential pair. Also usb maybe backwards
2023-10-13 Create README.md
    Read me
2023-10-13 Update README.md
    removed #
2023-10-13 Removed resistor at the ina- termina
2023-10-16 added a new pcb practice
2023-10-17 tweaked some stuff for the daq and added a files
2023-10-18 started prepping for fab
2023-10-22 added production files
2023-10-24 Add submodules
2023-10-24 added symbol and pcb footprints
2023-10-28 added mx style swithches to the keyboard pcb
2023-10-28 added caps to the voltage regulator also gerber and position files need to be updated
2023-10-28 changes to keyboard structure
2023-10-28 reverted back to a version where the caps were not added to the voltage regulator
2023-10-28 removed tooling holes from the pcb
2023-10-29 added a new board for a more cost effective option
2023-10-30 finished the schematic and most of the PCB just need the PWR planes and routes
2023-10-31 finished the PCB just need to double check everything is good
2023-11-01 edits to the pcb
2023-11-26 added a new folder for a new pcb
2023-11-26 added another gerber file
2023-12-25 added a new pcb based on the stm32f429zit board
2024-01-17 finished schematics and mostly finished the routing for the pcb
2024-01-17 added changes to the rev 2 board
2024-01-17 finished routing for stm32f429
2024-01-19 removed alot of the silk screen, changed oscillator foor print and added GPIOs
2024-01-19 changed logging schematic, tweaked some parts of the schematic
2024-01-20 added another folder for a CAN Node PCB
2024-01-20 changed some footprints, removed dimensions( was causing issues), addd a gerber filter for manufacturing(probably should be regenerated), added a BOM list
2024-01-20 added a folder for custom footprints and added more vias on the 5V and the gnd planes
2024-01-22 usb footprint changes, Silkscreen markers for pin 1 in ICs and polarity for other components. Edited excel BOM list and kicad list for BOM cost.
2024-01-22 finished the CAN IMU schematic and pcb. Only needs some final touhces and a BOM list
2024-01-23 modified gerber and bom
2024-01-23 redid the manufacturing folder to get it to be compatible with JLC
2024-01-24 added logo to the back silkscreen
2024-01-29 increased the size of the pin 1 dot
2024-01-29 started new schematic for enabling CAN on a LSM6DSOX
2024-01-31 Started pcb with component placement and physical size constraints
2024-01-31 started the routing process for the CAN LSM6DSOX
2024-02-01 almost finished routing just need to solve clearance issues and route 5V with a potential power plane
2024-02-01 decided to connect 5V connections directly instead of making a power plane. Probably should change this later
2024-02-02 moved SWD to the left side divided the power plane between 3.3 and 5v and did some rerouting of traces
2024-02-05 added DFR logo,revision number, and the current date
2024-02-08 updated some stuff
2024-02-09 changed the usb A connector
2024-02-17 something
2024-02-18 started the rev 2 design with basic stm32 necessary circuits
2024-02-19 done most of the schematic. I think I just need to do USB, Maybe SPI ( if needed),USB data, and some more I2C lines or another UART
2024-02-25 got the pcb into size constraint now need to try and see if routing is possible
2024-02-25 did like a quarter of the routing
2024-02-26 finished the pcb routing except the usb C now I just need to do the DRC
2024-03-10 added a new schematic that is a copy of the rat pro distortion pedal
2024-03-10 finished distortion pcb but kinda want to rethink how to approach this pcb
2024-03-10 added finishing touches to the rev 2 design
2024-03-14 added some silkscreen to to differentiate parts
2024-03-15 added the most important part, Cat silkscreen. Also added DFR logo,revision number, and the todays date( even though this was finished a while ago)
2024-03-17 tweaked the differential traces and made thhem compliant to JLC04161H-7628 guidlines for controlled impedance. Also I think I might remove the 10 pin header for SWD/JTAG in favor of just SWD to safe 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
2024-03-18 removed the 10 pin SWD/JTAG header in favor of just a 3 pin SWD connector.in addition, also added a 3.3V and a 5V header for external power supplies
2024-03-19 created BOM and CPL and removed the 10 pin JTAG/SWD in favor of just 3 pins for SWD
2024-03-20 added another op amp to the delay
2024-03-25 redid the traces for the LSM6DSOX CAN PCB. Also created the BOM and the CPL files for manufacturing. Which means this board should be ready to get sent to pcb manufacturing.
2024-03-25 added the BOM and the CPL files because the gitignore blocked a csv so I needed to remove that ignore
2024-03-25 changed pin one identifier that is on the ldo
2024-03-29 ethernet file added altered the lsm6dsox cpl
2024-03-29 BOM and CPL stm32f429
2024-04-06 added a second version of revision 2
2024-04-06 fixed some wiring issues where a wire wasn't connected well
2024-04-06 re-adding files something happened with last commit
2024-04-07 finished the schematic and footprint assignment
2024-04-08 added pull up resistors to the I2c Lines for LSM and did mock up placements for PCB
2024-04-12 done about 2/3 of the routing for the board
2024-04-13 finished the first mock up of routing now just need to polish it up
2024-04-15 added the manufacturing files
2024-04-24 added molex cable library to the rev2
2024-04-24 added user zone fills to section out the PCB into different sections
2024-04-30 added USART6 to some pin headers and added more labels and color codes to th schematic
2024-06-12 added a breakout sensor for analog not finished
2024-06-13 added a different version of rev 2.1 called 2.2 not finished yet
2024-06-13 changed layer stack up to sig,gnd,gnd, sig/power and routing according to the new stackup
2024-06-14 added a usb C for power delivery and moved voltage regulator and readjusted the partial power plane to fit the USB C
2024-06-15 added manufacturing files
2024-06-15 updated gerber files to reflect some partial power plane adjustments
2024-06-28 added labels that tell you which pins the connectors are connected to for analog, GPIO, and LEDs. Also added a label for the USB C connector called Power to indicate its function
2024-07-02 added a new PCB project with parts of the schematic done
2024-07-02 added layouts in both json and png form
2024-07-02 added some more the the keyboard schematic
2024-07-05 first iteration of the keyboard schematic
2024-07-08 added pictures of daq board, updated esc to finish on three phase control
2024-07-08 finished first mock up of the esc scheamtic still need to check everything works tho
2024-07-10 finished a mockup of the pcb layout
2024-07-11 did some of the routing ofthe PCB
2024-09-11 finished the pcb layout of the ESC and now need to be revised to make sure everything is correct
2024-10-18 created a tube screamer schematic that was from Electrosmash.com
2024-10-24 added values to some components that i forgot to add
2024-10-29 some edits to the tubescreamer schematic and added another file for treble boost
2024-10-29 finished the schematic
2024-11-11 added a new schematic for multifx
2024-12-28 removed the multifx folder was causing some bugs
2024-12-29 added a wien-bridge circuit schematic that needs pcb to be done
2024-12-29 finished first revision of the pcb of wien-bridge
2024-12-30 few additions to the wein-brdige circuit and finished first revision of the opamp distortion schematic
2024-12-31 finished the first revision of the pcb schematic for op amp distortion
2024-12-31 editied the PCB
2024-12-31 added labeling to the pcb and made gerber 'wq
2024-12-31 compressed gerber and drill to a rar file
2025-01-01 combined distortion and wien-bridge schematics together for maunfacturing purposes
2025-01-05 decided to use one power supply for both circuits so redid the pcb to reflect that
2025-01-05 changed diodes to sod-123 package and changed pcb accordingly and create gerber,drill, pos,and BOM list for manufacturing
2025-01-05 removed lock file
2025-01-05 redid the manufacturing files since i had the wrong diode foot print
2025-01-07 added a new file for a pedal based tuner
2025-01-20 adjusted pre-amp, added digital pins for led, added LEDs drivers for LED
2025-01-24 added 4 LEDs to the PCB and finished using the ERC to verify errors
2025-01-31 finalized some stm32 necessities
2025-02-01 revision to the schematics then grouped components together for pcb layout
2025-02-04 removed the LED drivers and finished first layout placement for the PCB
2025-03-21 added a new project
2025-03-25 changed up the ESC schematic
